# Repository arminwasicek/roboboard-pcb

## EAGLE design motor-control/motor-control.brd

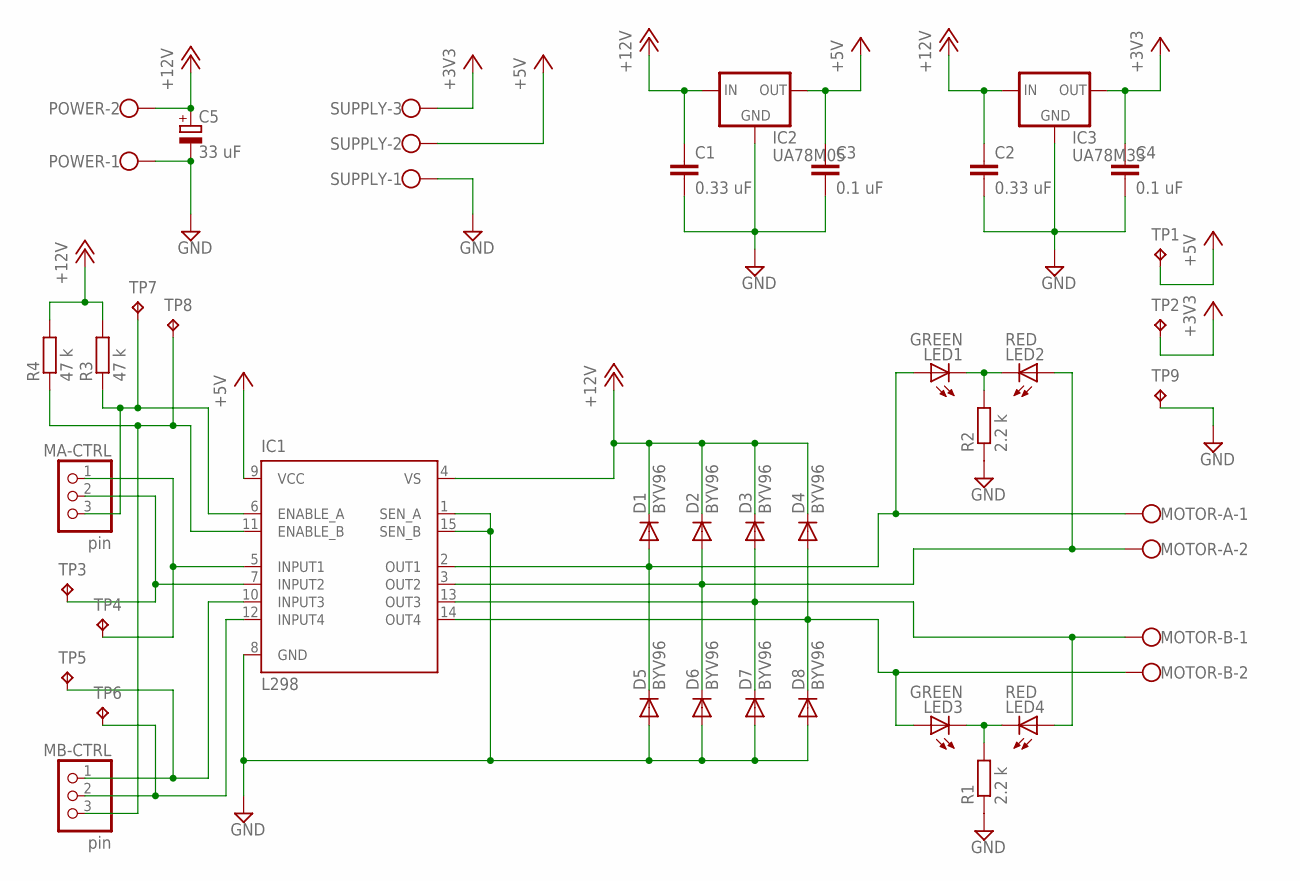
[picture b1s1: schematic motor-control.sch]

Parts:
C1, C2: 0.33 uF; C050-024X044
C3, C4: 0.1 uF; C050-024X044
C5: 33 uF; E2,5-5
D1, D2, D3, D4, D5, D6, D7, D8: BYV96; SOD57-10
IC1: L298; MULTIWATT-15
IC2: UA78M05; 78XXS
IC3: UA78M33; 78XXS
LED1, LED3: GREEN; LED5MM
LED2, LED4: RED; LED5MM
MA-CTRL: pin; 1X03
MB-CTRL: pin; 1X03
MOTOR-A: W237-02P; W237-132
MOTOR-B: W237-02P; W237-132
POWER: W237-02P; W237-132
R1, R2: 2.2 k; 0207/7
R3, R4: 47 k; 0207/7
SUPPLY: W237-03P; W237-133
TP1, TP2, TP3, TP4, TP5, TP6, TP7, TP8, TP9: TPTP14SQ; TP14SQ

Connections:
+3V3: C4.1, IC3.OUT, SUPPLY.3, TP2.TP
+5V: C3.1, IC1.9 (VCC), IC2.OUT, SUPPLY.2, TP1.TP
+12V: C1.1, C2.1, C5.+, D1.C, D2.C, D3.C, D4.C, IC1.4 (VS), IC2.IN, IC3.IN, POWER.2, R3.2, R4.2
GND: C1.2, C2.2, C3.2, C4.2, C5.-, D5.A, D6.A, D7.A, D8.A, IC1.1 (SEN_A), IC1.8 (GND), IC1.15 (SEN_B), IC2.GND, IC3.GND, POWER.1, R1.1, R2.1, SUPPLY.1, TP9.TP
unnamed: D1.A, D5.C, IC1.2 (OUT1), LED1.A, MOTOR-A.1
unnamed: LED3.K (C), LED4.K (C), R1.2
unnamed: LED1.K (C), LED2.K (C), R2.2
unnamed: IC1.10 (INPUT3), MB-CTRL.1, TP5.TP
unnamed: IC1.12 (INPUT4), MB-CTRL.2, TP6.TP
unnamed: D4.A, D8.C, IC1.14 (OUT4), LED3.A, MOTOR-B.2
unnamed: IC1.5 (INPUT1), MA-CTRL.1, TP4.TP
unnamed: IC1.7 (INPUT2), MA-CTRL.2, TP3.TP
unnamed: IC1.6 (ENABLE_A), MA-CTRL.3, R3.1, TP7.TP
unnamed: IC1.11 (ENABLE_B), MB-CTRL.3, R4.1, TP8.TP
unnamed: D2.A, D6.C, IC1.3 (OUT2), LED2.A, MOTOR-A.2
unnamed: D3.A, D7.C, IC1.13 (OUT3), LED4.A, MOTOR-B.1

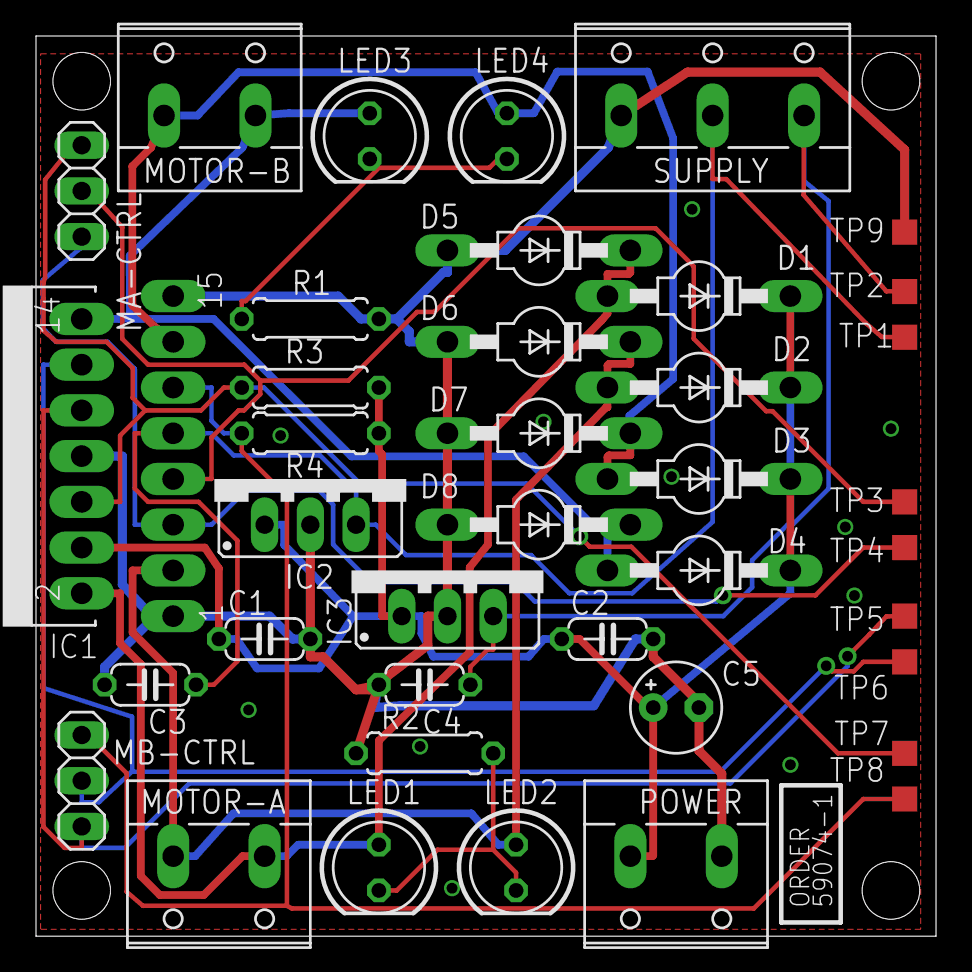
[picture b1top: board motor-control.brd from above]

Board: 2 copper layers, 50.0 x 50.0 mm, 39 parts (0 on the bottom side), 16 nets.

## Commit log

2014-02-23 Added motor-control.
2014-02-23 Added lfsensor.
